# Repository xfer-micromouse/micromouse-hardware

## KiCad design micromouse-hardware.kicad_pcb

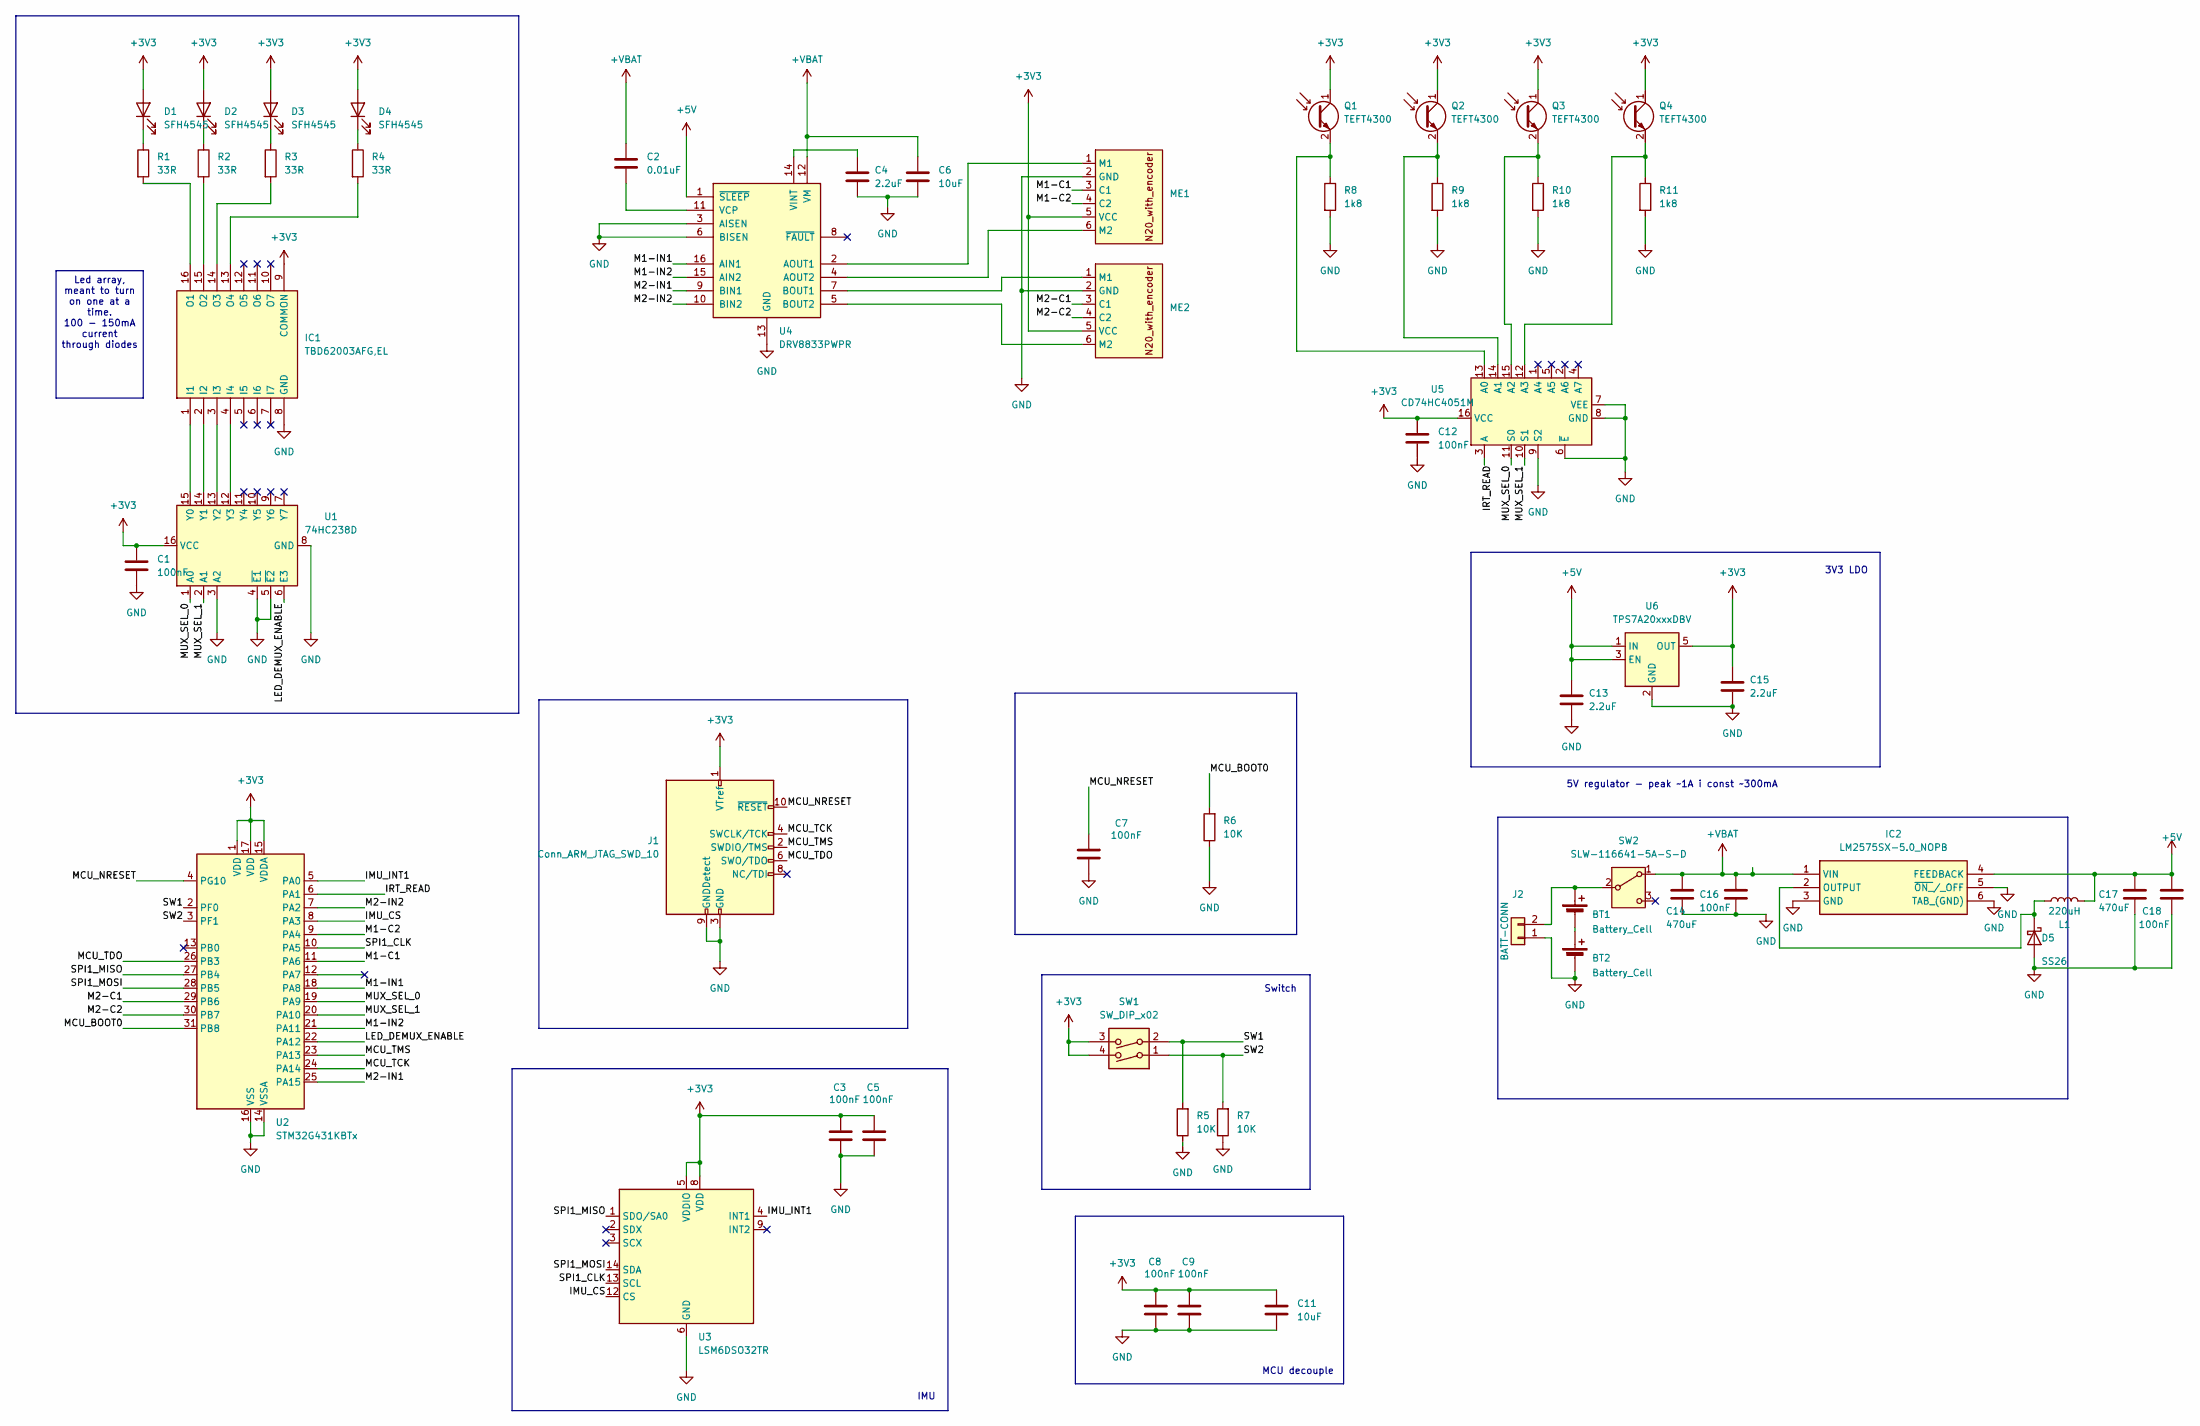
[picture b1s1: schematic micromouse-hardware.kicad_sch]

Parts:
BT1, BT2: Battery_Cell; PinHeader_1x02_P2.54mm_Vertical
C1, C3, C5, C7, C8, C9, C12, C16, C18: 100nF; C_0805_2012Metric_Pad1.18x1.45mm_HandSolder; Manufacturer_Part_Number KAM21BR71H104JM
C2: 0.01uF; C_0805_2012Metric_Pad1.18x1.45mm_HandSolder; Manufacturer_Part_Number KAF21BR72A103JT
C4, C13, C15: 2.2uF; C_0805_2012Metric_Pad1.18x1.45mm_HandSolder; Manufacturer_Part_Number KAF21KR71E225KU
C6, C11: 10uF; C_0805_2012Metric_Pad1.18x1.45mm_HandSolder; Manufacturer_Part_Number MCASL21GBB7106KTNA01
C14, C17: 470uF; C_Elec_8x10.2; Manufacturer_Part_Number EDK477M016A9MAA
D1, D2, D3, D4: SFH4545; LED_D5.0mm_Horizontal_O3.81mm_Z3.0mm; Manufacturer_Part_Number SFH 4545
D5: SS26; D_SMA; Manufacturer_Part_Number SS26SHE3_B/H
IC1: TBD62003AFG,EL; SOIC127P630X190-16N; Mouser Part Number 757-TBD62003AFGEL
IC2: LM2575SX-5.0_NOPB; KTT0005B; Mouser Part Number 926-LM2575SX-5.0NOPB
J1: Conn_ARM_JTAG_SWD_10; PinHeader_2x05_P1.27mm_Vertical_SMD
J2: BATT-CONN; PinHeader_1x02_P2.54mm_Vertical
L1: 220uH; L_12x12mm_H8mm; Manufacturer_Part_Number SRR1280-221K
ME1, ME2: PinHeader_1x06_P2.54mm_Vertical_SMD_Pin1Left
Q1, Q2, Q3, Q4: TEFT4300; LED_D3.0mm_Horizontal_O3.81mm_Z2.0mm; Manufacturer_Part_Number TEFT4300
R1, R2, R3, R4: 33R; R_0805_2012Metric_Pad1.20x1.40mm_HandSolder; Manufacturer_Part_Number CRGS0805J33R
R5, R6, R7: 10K; R_0805_2012Metric_Pad1.20x1.40mm_HandSolder; Manufacturer_Part_Number CHP0805-FX-1002ELF
R8, R9, R10, R11: 1k8; R_Axial_DIN0207_L6.3mm_D2.5mm_P10.16mm_Horizontal; Manufacturer_Part_Number SFR25H0001801JA500
SW1: SW_DIP_x02; SW_DIP_SPSTx02_Slide_9.78x7.26mm_W7.62mm_P2.54mm; Manufacturer_Part_Number 206-2ST
SW2: SLW-116641-5A-S-D; PinHeader_1x03_P2.54mm_Vertical; Manufacturer_Part_Number EG1218
U1: 74HC238D; SOIC-16_3.9x9.9mm_P1.27mm; Manufacturer_Part_Number 74HC238D
U2: STM32G431KBTx; LQFP-32_7x7mm_P0.8mm
U3: LSM6DSO32TR; LGA-14_3x2.5mm_P0.5mm_LayoutBorder3x4y
U4: DRV8833PWPR; HTSSOP-16-1EP_4.4x5mm_P0.65mm_EP3.4x5mm; Manufacturer_Part_Number DRV8833CPWPR
U5: CD74HC4051M; SOIC-16_3.9x9.9mm_P1.27mm; Manufacturer_Part_Number CD74HC4051M
U6: TPS7A20xxxDBV; SOT-23-5

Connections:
+3V3: C1.1, C3.1, C5.1, C8.1, C9.1, C11.1, C12.1, C15.1, D1.2 (A), D2.2 (A), D3.2 (A), D4.2 (A), IC1.9 (COMMON), J1.1 (VTref), ME1.5 (VCC), ME2.5 (VCC), Q1.1 (C), Q2.1 (C), Q3.1 (C), Q4.1 (C), SW1.3, SW1.4, U1.16 (VCC), U2.1 (VDD), U2.15 (VDDA), U2.17 (VDD), U3.5 (VDDIO), U3.8 (VDD), U5.16 (VCC), U6.5 (OUT)
+5V: C13.1, C17.1, C18.1, IC2.4 (FEEDBACK), L1.2, U4.1 (~SLEEP), U6.1 (IN), U6.3 (EN)
+VBAT: C2.1, C6.1, C14.1, C16.1, IC2.1 (VIN), SW2.1 (A), U4.12 (VM)
/IMU_CS: U2.8 (PA3), U3.12 (CS)
/IMU_INT1: U2.5 (PA0), U3.4 (INT1)
/IRT_READ: U2.6 (PA1), U5.3 (A)
/LED_DEMUX_ENABLE: U1.6 (E3), U2.22 (PA12)
/M1-C1: ME1.3 (C1), U2.11 (PA6)
/M1-C2: ME1.4 (C2), U2.9 (PA4)
/M1-IN1: U2.18 (PA8), U4.16 (AIN1)
/M1-IN2: U2.21 (PA11), U4.15 (AIN2)
/M2-C1: ME2.3 (C1), U2.29 (PB6)
/M2-C2: ME2.4 (C2), U2.30 (PB7)
/M2-IN1: U2.25 (PA15), U4.9 (BIN1)
/M2-IN2: U2.7 (PA2), U4.10 (BIN2)
/MCU_BOOT0: R6.2, U2.31 (PB8)
/MCU_NRESET: C7.1, J1.10 (~RESET), U2.4 (PG10)
/MCU_TCK: J1.4 (SWCLK/TCK), U2.24 (PA14)
/MCU_TDO: J1.6 (SWO/TDO), U2.26 (PB3)
/MCU_TMS: J1.2 (SWDIO/TMS), U2.23 (PA13)
/MUX_SEL_0: U1.1 (A0), U2.19 (PA9), U5.11 (S0)
/MUX_SEL_1: U1.2 (A1), U2.20 (PA10), U5.10 (S1)
/SPI1_CLK: U2.10 (PA5), U3.13 (SCL)
/SPI1_MISO: U2.27 (PB4), U3.1 (SDO/SA0)
/SPI1_MOSI: U2.28 (PB5), U3.14 (SDA)
/SW1: R5.2, SW1.2, U2.2 (PF0)
/SW2: R7.2, SW1.1, U2.3 (PF1)
GND: BT2.2 (-), C1.2, C3.2, C4.2, C5.2, C6.2, C7.2, C8.2, C9.2, C11.2, C12.2, C13.2, C14.2, C15.2, C16.2, C17.2, C18.2, D5.2 (A), IC1.8 (GND), IC2.3 (GND), IC2.5 (~ON_/_OFF), IC2.6 (TAB_(GND)), J1.3 (GND), J1.5 (GND), J1.9 (GNDDetect), J2.1, ME1.2 (GND), ME2.2 (GND), R5.1, R6.1, R7.1, R8.2, R9.2, R10.2, R11.2, U1.3 (A2), U1.4 (~E1), U1.5 (~E2), U1.8 (GND), U2.14 (VSSA), U2.16 (VSS), U2.32 (VSS), U3.6 (GND), U3.7 (GND), U4.3 (AISEN), U4.6 (BISEN), U4.13 (GND), U4.17 (GND), U5.6 (~E), U5.7 (VEE), U5.8 (GND), U5.9 (S2), U6.2 (GND)
unnamed: BT1.2 (-), BT2.1 (+)
unnamed: D1.1 (K), R1.1
unnamed: D2.1 (K), R2.1
unnamed: D3.1 (K), R3.1
unnamed: D4.1 (K), R4.1
unnamed: D5.1 (K), IC2.2 (OUTPUT), L1.1
unnamed: IC1.1 (I1), U1.15 (Y0)
unnamed: IC1.2 (I2), U1.14 (Y1)
unnamed: IC1.3 (I3), U1.13 (Y2)
unnamed: IC1.4 (I4), U1.12 (Y3)
unnamed: IC1.16 (O1), R1.2
unnamed: IC1.15 (O2), R2.2
unnamed: IC1.14 (O3), R3.2
unnamed: IC1.13 (O4), R4.2
unnamed: BT1.1 (+), J2.2, SW2.2 (B)
unnamed: ME1.1 (M1), U4.2 (AOUT1)
unnamed: ME1.6 (M2), U4.4 (AOUT2)
unnamed: ME2.1 (M1), U4.7 (BOUT1)
unnamed: ME2.6 (M2), U4.5 (BOUT2)
unnamed: Q1.2 (E), R8.1, U5.13 (A0)
unnamed: Q2.2 (E), R9.1, U5.14 (A1)
unnamed: Q3.2 (E), R10.1, U5.15 (A2)
unnamed: Q4.2 (E), R11.1, U5.12 (A3)
unnamed: C2.2, U4.11 (VCP)
unnamed: C4.1, U4.14 (VINT)

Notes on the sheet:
MCU decouple
5V regulator - peak ~1A i const ~300mA
3V3 LDO
IMU
Switch
Led array, meant to turn on one at a time. 100 - 150mA current through diodes

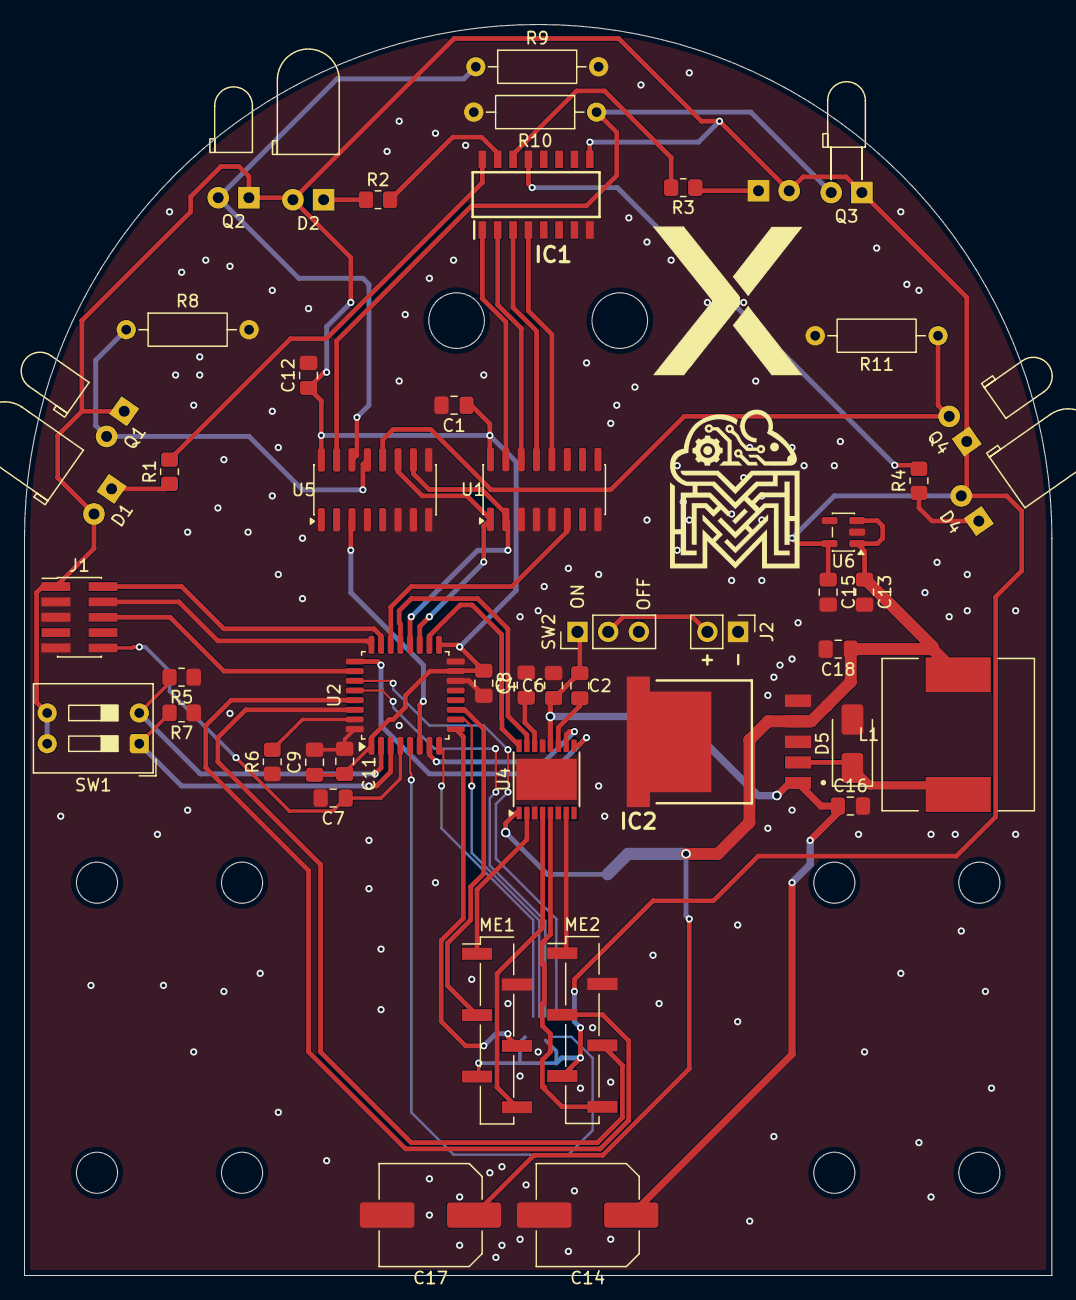
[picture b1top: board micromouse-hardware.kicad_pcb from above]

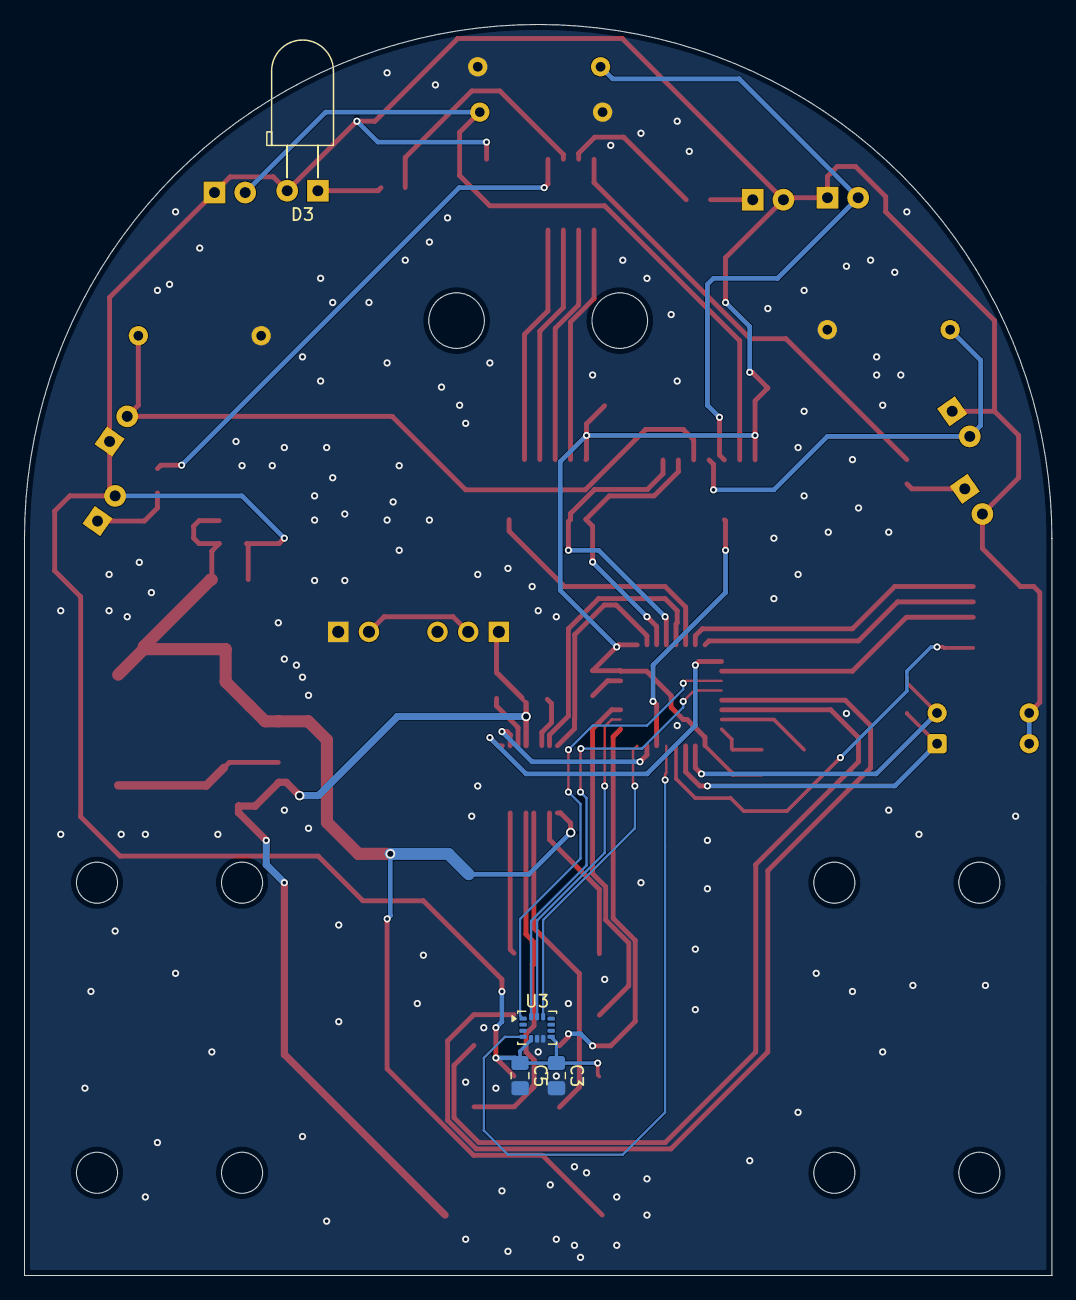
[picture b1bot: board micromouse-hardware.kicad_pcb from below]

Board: 2 copper layers, 85.0 x 103.5 mm, 52 parts (4 on the bottom side), 52 nets.

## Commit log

2025-03-18 second commit
2025-03-19 before routing
2025-10-23 nesto stabilno
2025-10-23 before arduino rotae
2025-10-24 everything except ground plane
2025-11-12 limit
2025-11-13 Arduino Nano - Regulated 5V should be connected to 5V not VIN Moved some labels around to make connections more visible Placed No Connect Flags on all unused pins Added descriptive names to labels Ch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
2025-11-20 Change the transistor footprint, changed spacing around the components to allow for mounting hardware to be added
2026-02-02 promjenio tranistore u mosfete, jos neki popravci
2026-02-02 PCB clean up
2026-04-22 kao gotov al da se poboljsat pcb
2026-04-22 slikica
